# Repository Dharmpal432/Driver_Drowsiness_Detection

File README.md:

# Smart Driver Drowsiness Detection & Alert System

A simulation based Driver Drowsiness Detection and Alert System developed using OpenCV, Python, Arduino simulation, and KiCad PCB design.

The project demonstrates how computer vision can be used to detect a driver's eyes and identify possible drowsiness, while an embedded alert circuit provides LED and buzzer indications.

---

##  Project Overview

Driver drowsiness is a major safety concern while driving. This project demonstrates a basic system that monitors the driver's face and eyes using a camera.

The system detects the face, detects the eyes, and monitors whether the eyes remain undetected for a certain period. If prolonged eye closure is detected, the system generates a drowsiness alert.

The project was developed completely as a simulation and learning project without physical hardware.

---

##  Objectives

- Detect the driver's face using a camera.
- Detect the driver's eyes using OpenCV.
- Identify possible drowsiness based on eye detection.
- Generate an alert when drowsiness is detected.
- Simulate an LED and buzzer alert circuit.
- Design a PCB for the alert circuit using KiCad.
- Understand the complete development flow from simulation to computer vision.

---

##  System Architecture

```text
Camera
   ↓
Python + OpenCV
   ↓
Face Detection
   ↓
Eye Detection
   ↓
Eye Closure Monitoring
   ↓
Drowsiness Decision
   ↓
Drowsiness Alert

```

## Working Principle
### 1. Camera Input
The system captures live video using the computer's camera.

### 2. Face Detection
OpenCV's Haar Cascade classifier detects the driver's face.

### 3. Eye Detection
The detected face region is analyzed to detect the eyes.

### 4. Drowsiness Detection
The system continuously checks whether the eyes are detected.

If the eyes are not detected for a predefined number of frames, the system considers the driver to be drowsy.

### 5. Alert
When drowsiness is detected, the system displays a warning message and produces an audible alert.

---

## Technologies & Tools Used
- Python
- OpenCV
- Haar Cascade Classifier
- Arduino
- Wokwi
- KiCad
- Computer Vision
- PCB Design
- Gerber File Generation

---

## Project Structure
```text
Driver_Drowsiness_Detection/
│
├── README.md
│
├── Wokwi_Simulation/
│   ├── diagram.json
│   ├── sketch.ino
│   └── wokwi-project.txt
│
├── KiCad_PCB/
│   ├── Driver_Drowsiness_System.kicad_pcb
│   ├── Driver_Drowsiness_System.kicad_pro
│   ├── Driver_Drowsiness_System.kicad_sch
│   └── Gerber/
│
└── OpenCV_Drowsiness_Detection/
    ├── camera_test.py
    ├── face_detect.py
    ├── eye_detect.py
    ├── drowsiness_detection.py
    │
    └── screenshots/
        ├── camera_test_success.png
        ├── face_detection_success.png
        ├── eye_detection_success.png
        ├── drowsiness_normal.png
        └── drowsiness_alert.png

```

## OpenCV Implementation

The computer vision part of the project contains four Python programs.

## Camera Test

[`camera_test.py`](OpenCV_Drowsiness_Detection/camera_test.py)

Tests whether the computer camera can successfully capture live video.

## Face Detection

[`face_detect.py`](OpenCV_Drowsiness_Detection/face_detect.py)

Uses OpenCV Haar Cascade to detect the driver's face.
## Eye Detection

[`eye_detect.py`](OpenCV_Drowsiness_Detection/eye_detect.py)

Detects the eyes inside the detected face region.
## Drowsiness Detection

[`drowsiness_detection.py`](OpenCV_Drowsiness_Detection/drowsiness_detection.py)

Combines face and eye detection and monitors eye visibility.
If the eyes remain undetected for a predefined number of frames, the system displays:
DROWSINESS ALERT!
and generates an audible warning.

## Wokwi Simulation
The embedded alert circuit is simulated using Arduino in Wokwi.
Components
- Arduino Uno
- Push Button
- LED
- Buzzer

SIMULATION LOGIC
```text
Button Press
     ↓
Duration Monitoring
     ↓
Normal → Drowsy → Warning → Critical
     ↓
LED + Buzzer Alert
```
The push button is used to simulate different driver conditions.

## KiCad PCB Design
The alert circuit was also designed as a PCB using KiCad.
The PCB design includes:
- Arduino Nano
- LED
- Resistor
- Push Button
- Buzzer
- PCB traces
- Ground plane
- Edge cuts
Gerber and drill files were generated for the PCB design.
The KiCad PCB design uses an Arduino Nano as the controller, while the Wokwi simulation uses an Arduino Uno to demonstrate the alert logic.

Note: The PCB was created as a design/simulation exercise and was not physically manufactured.

## Results
### Camera Test

### Face Detection

### Eye Detection

### Normal Condition

### Drowsiness Alert

##  Features
- Real-time camera monitoring
- Face detection
- Eye detection
- Basic drowsiness detection
- Audible warning
- Arduino alert simulation
- PCB design
- Gerber file generation
- Completely simulation-based implementation

## Advantages
- Low-cost development approach
- No physical hardware required for testing
- Easy to understand and modify
- Combines embedded systems with computer vision
- Demonstrates the complete development workflow
- Useful for learning OpenCV and PCB design

## Limitations
- Haar Cascade detection can be affected by lighting conditions.
- Eye detection may not work reliably with glasses or extreme head angles.
- The current system uses a basic eye-detection approach rather than a sophisticated AI model.
- It is a learning and simulation project and should not be considered a safety-certified driving system.

## Future Scope
The project can be improved by:
- Using facial landmarks or Eye Aspect Ratio (EAR).
- Using MediaPipe or a deep-learning-based face/eye detector.
- Improving detection accuracy under different lighting conditions.
- Adding head-pose detection.
- Adding real embedded hardware integration.
- Connecting the computer vision system with an external alert controller.
- Adding GPS/GSM emergency notification features.
- Developing a more robust real-time driver monitoring system.

## Learning Outcomes
Through this project, I learned:
- Basics of computer vision.
- OpenCV camera handling.
- Face detection using Haar Cascade.
- Eye detection.
- Real-time video processing.
- Basic drowsiness detection logic.
- Arduino simulation using Wokwi.
- Schematic and PCB design using KiCad.
- Gerber file generation.
- Organizing a complete engineering project.

## Author
Dharmpal Pawar
Electronics & Telecommunication Engineering Student

## Project Status

**Completed – Simulation & Learning Prototype**

The project successfully demonstrates:

- Camera-based face detection
- Eye detection
- Basic drowsiness detection
- Audible drowsiness alert
- Arduino alert simulation
- KiCad schematic and PCB design
- Gerber file generation

No physical hardware was used in this project.

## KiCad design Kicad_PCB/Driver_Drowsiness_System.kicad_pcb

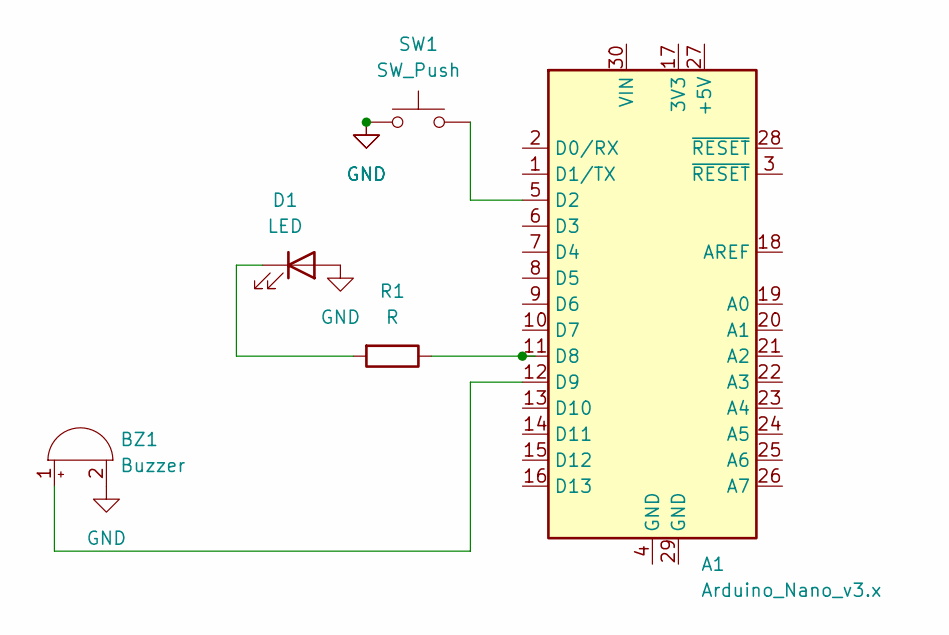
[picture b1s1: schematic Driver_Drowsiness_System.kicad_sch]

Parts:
A1: Arduino_Nano_v3.x; Arduino_Nano
BZ1: Buzzer; Buzzer_12x9.5RM7.6
D1: LED; LED_D5.0mm
R1: R; R_Axial_DIN0207_L6.3mm_D2.5mm_P7.62mm_Horizontal
SW1: SW_Push; SW_PUSH_6mm

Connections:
GND: BZ1.2 (-), D1.2 (A), SW1.1
unnamed: A1.5 (D2), SW1.2
unnamed: A1.11 (D8), R1.1
unnamed: A1.12 (D9), BZ1.1 (+)
unnamed: D1.1 (K), R1.2

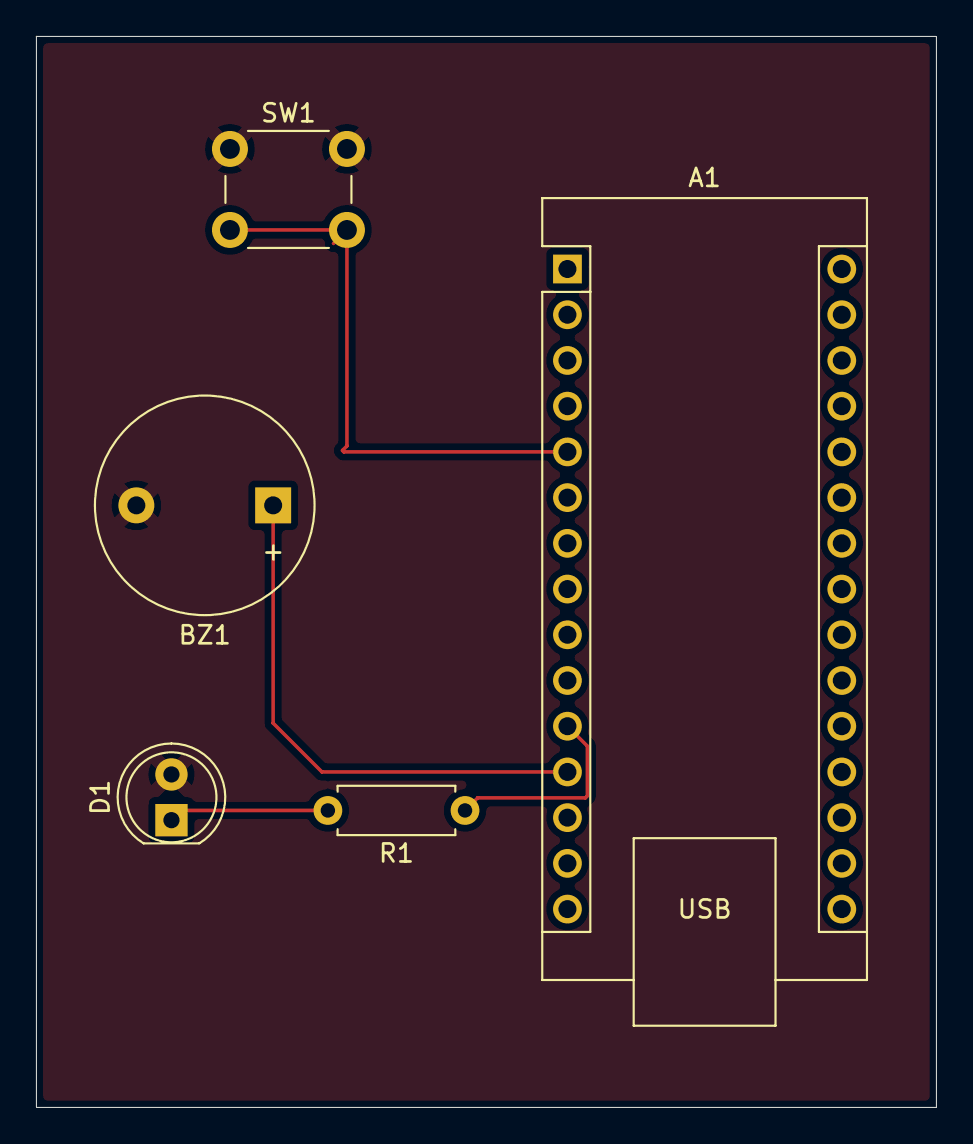
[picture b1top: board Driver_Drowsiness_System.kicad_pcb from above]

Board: 2 copper layers, 50.0 x 59.5 mm, 5 parts (0 on the bottom side), 5 nets.
